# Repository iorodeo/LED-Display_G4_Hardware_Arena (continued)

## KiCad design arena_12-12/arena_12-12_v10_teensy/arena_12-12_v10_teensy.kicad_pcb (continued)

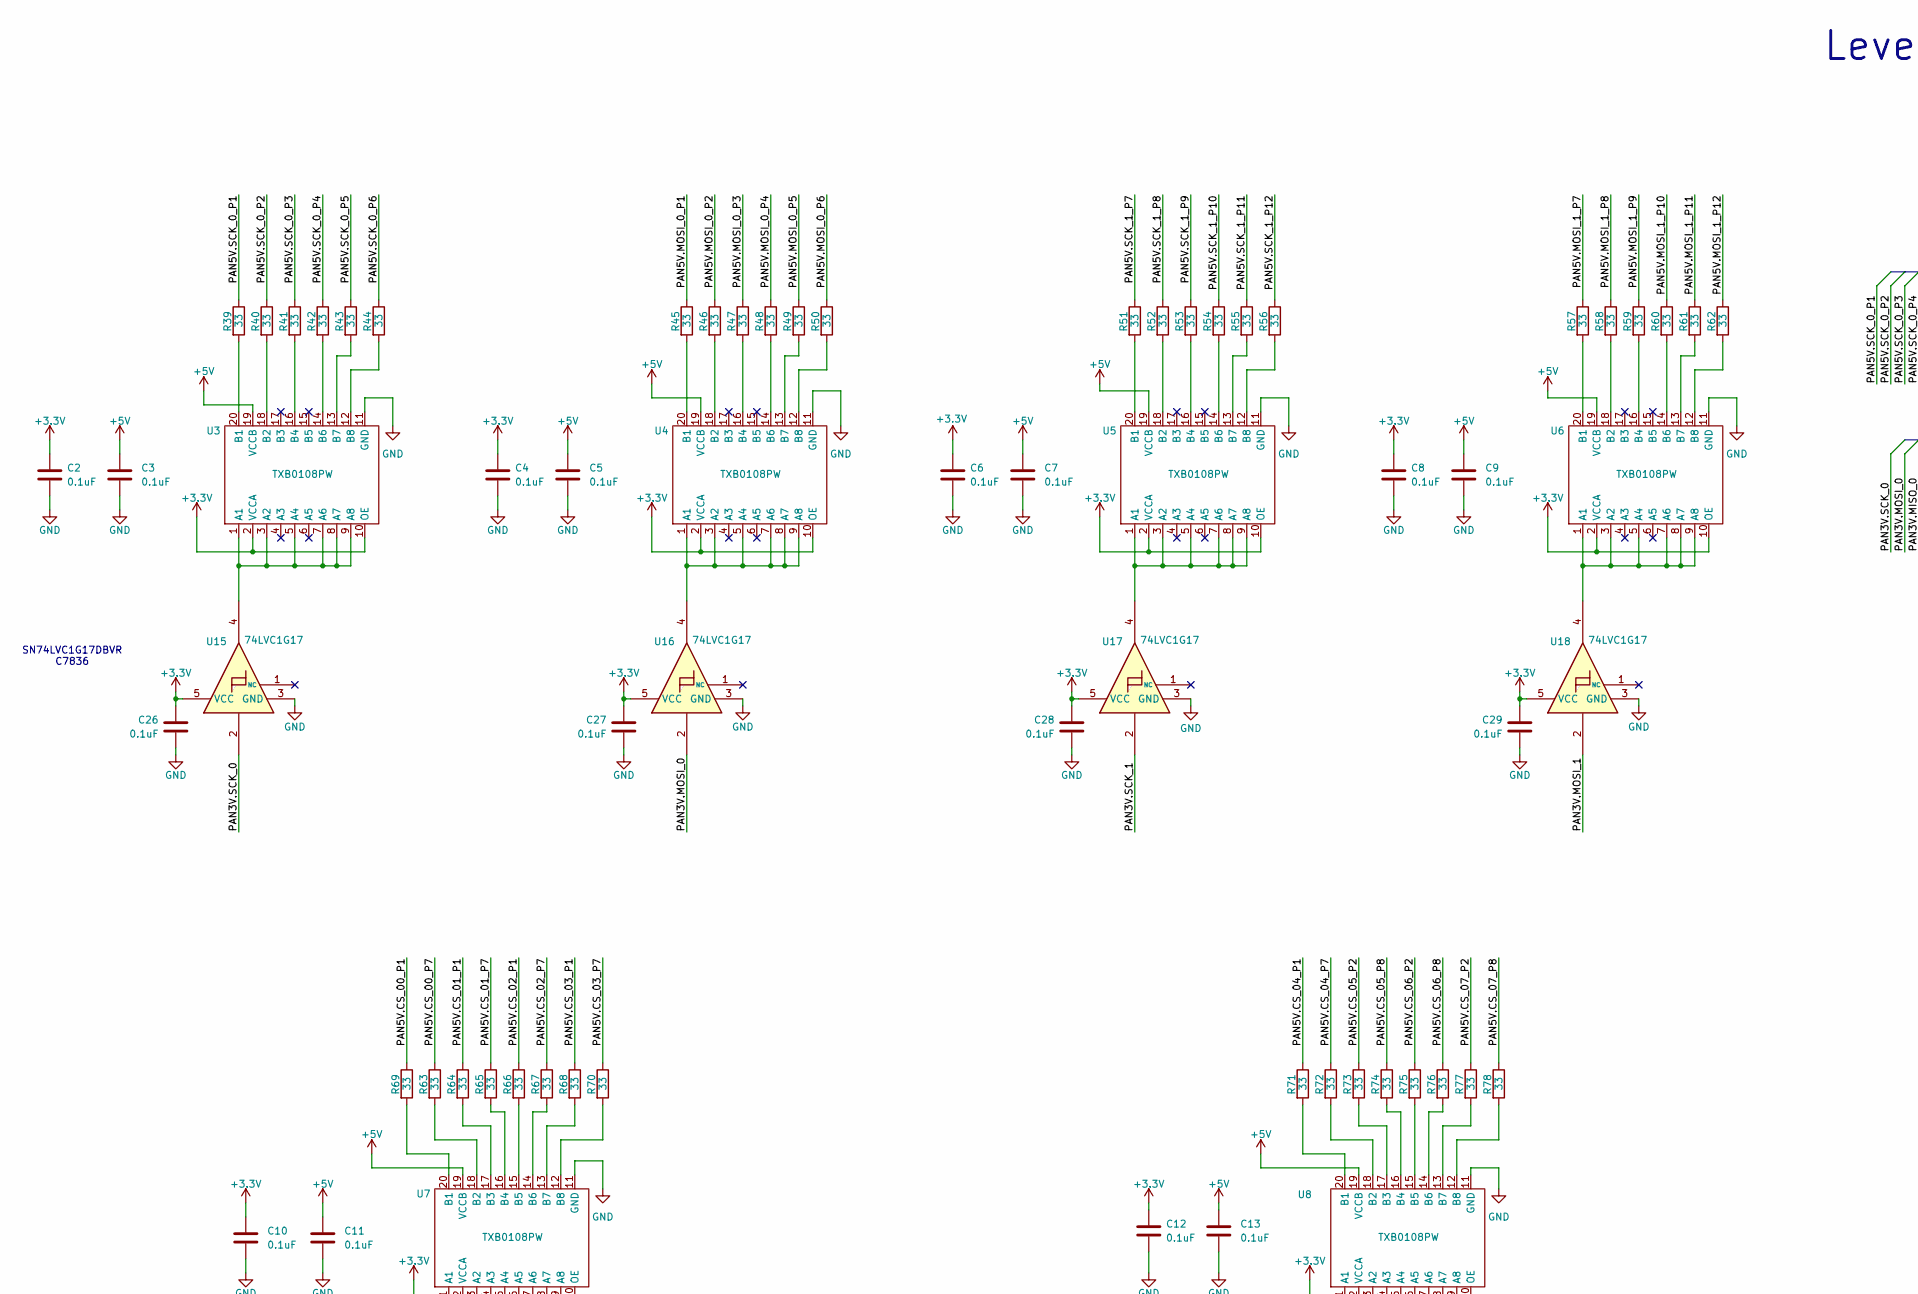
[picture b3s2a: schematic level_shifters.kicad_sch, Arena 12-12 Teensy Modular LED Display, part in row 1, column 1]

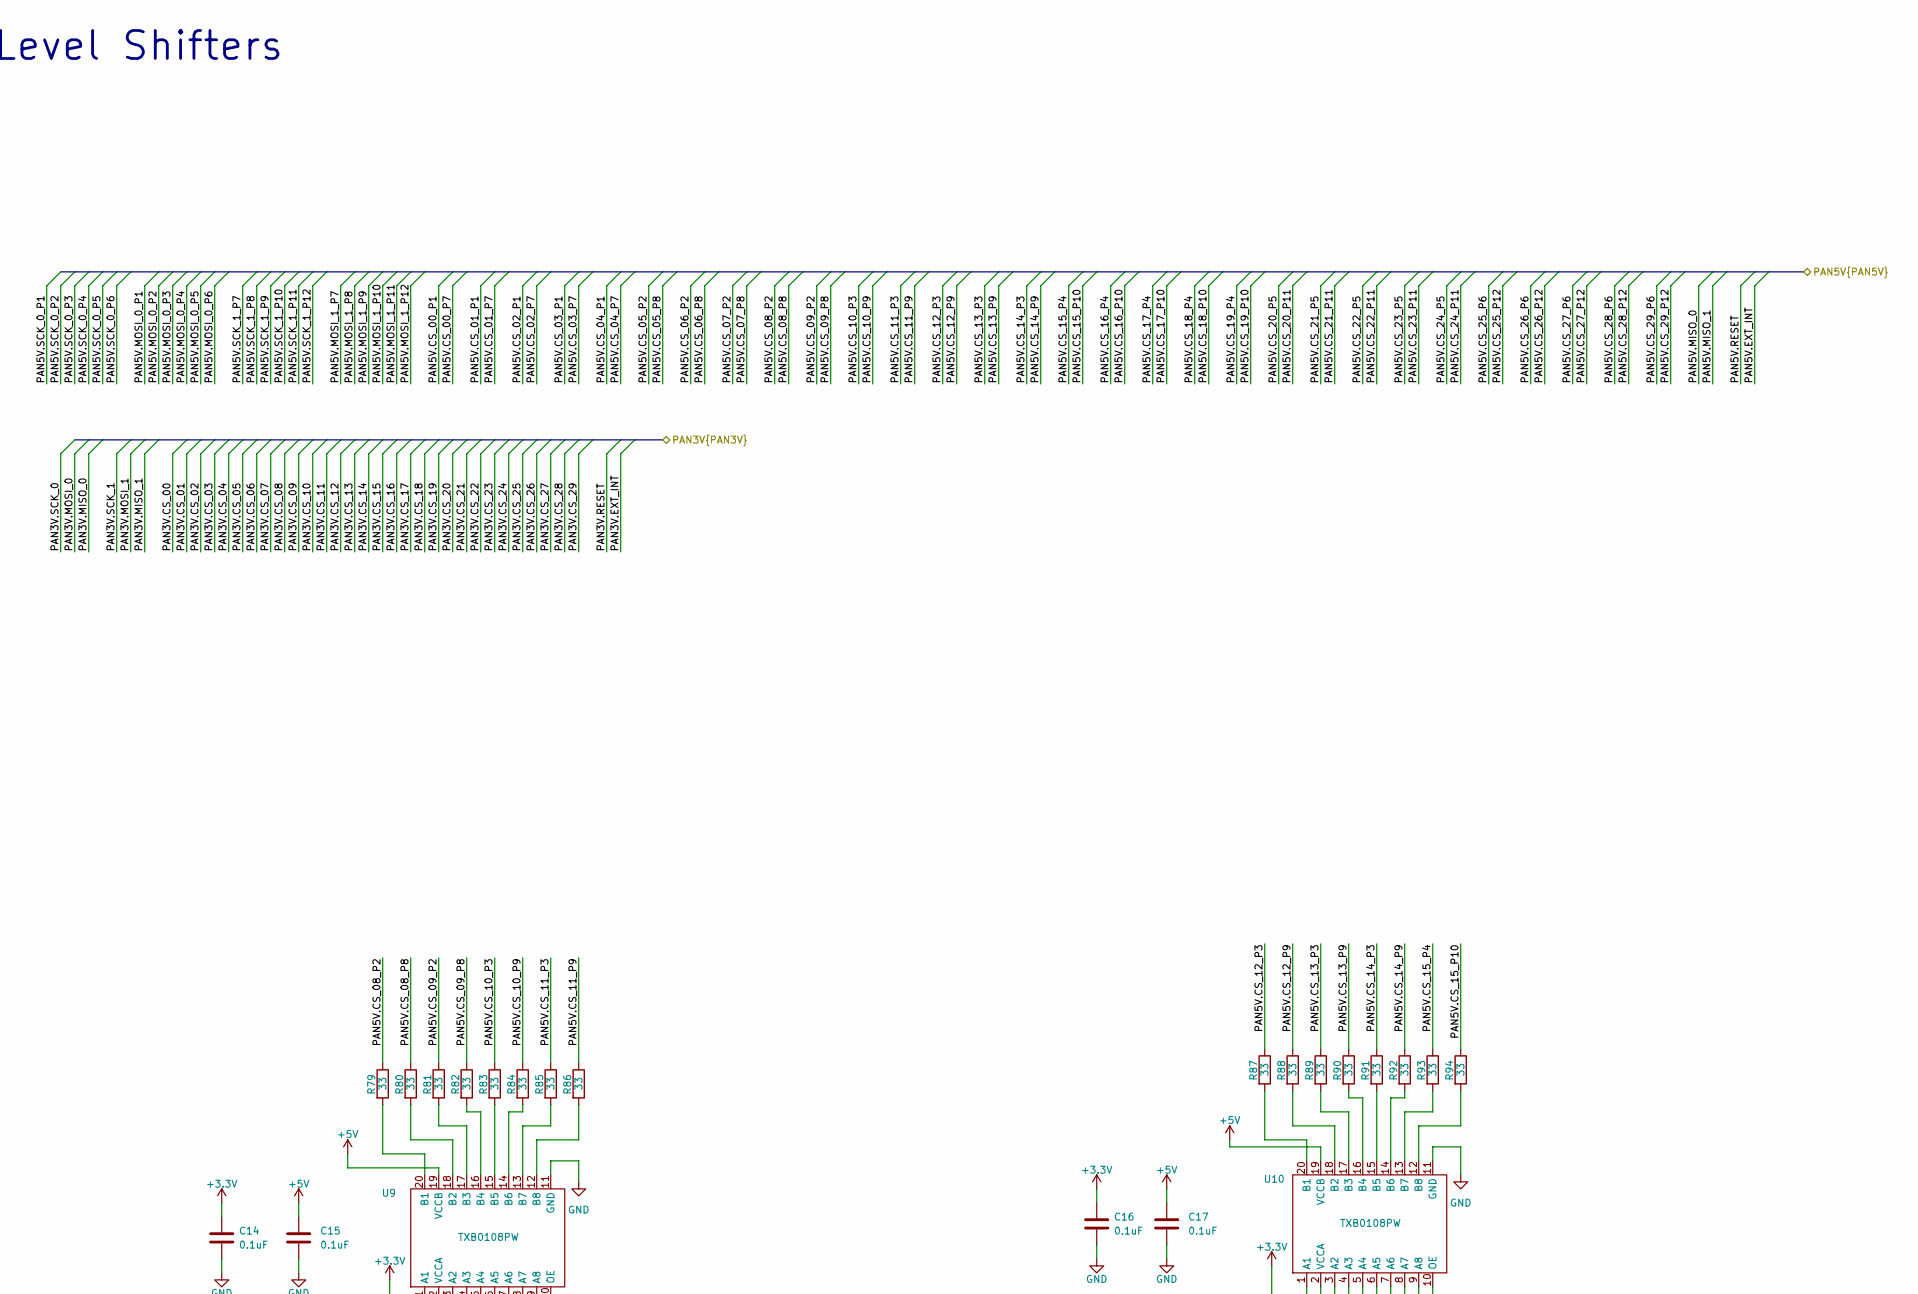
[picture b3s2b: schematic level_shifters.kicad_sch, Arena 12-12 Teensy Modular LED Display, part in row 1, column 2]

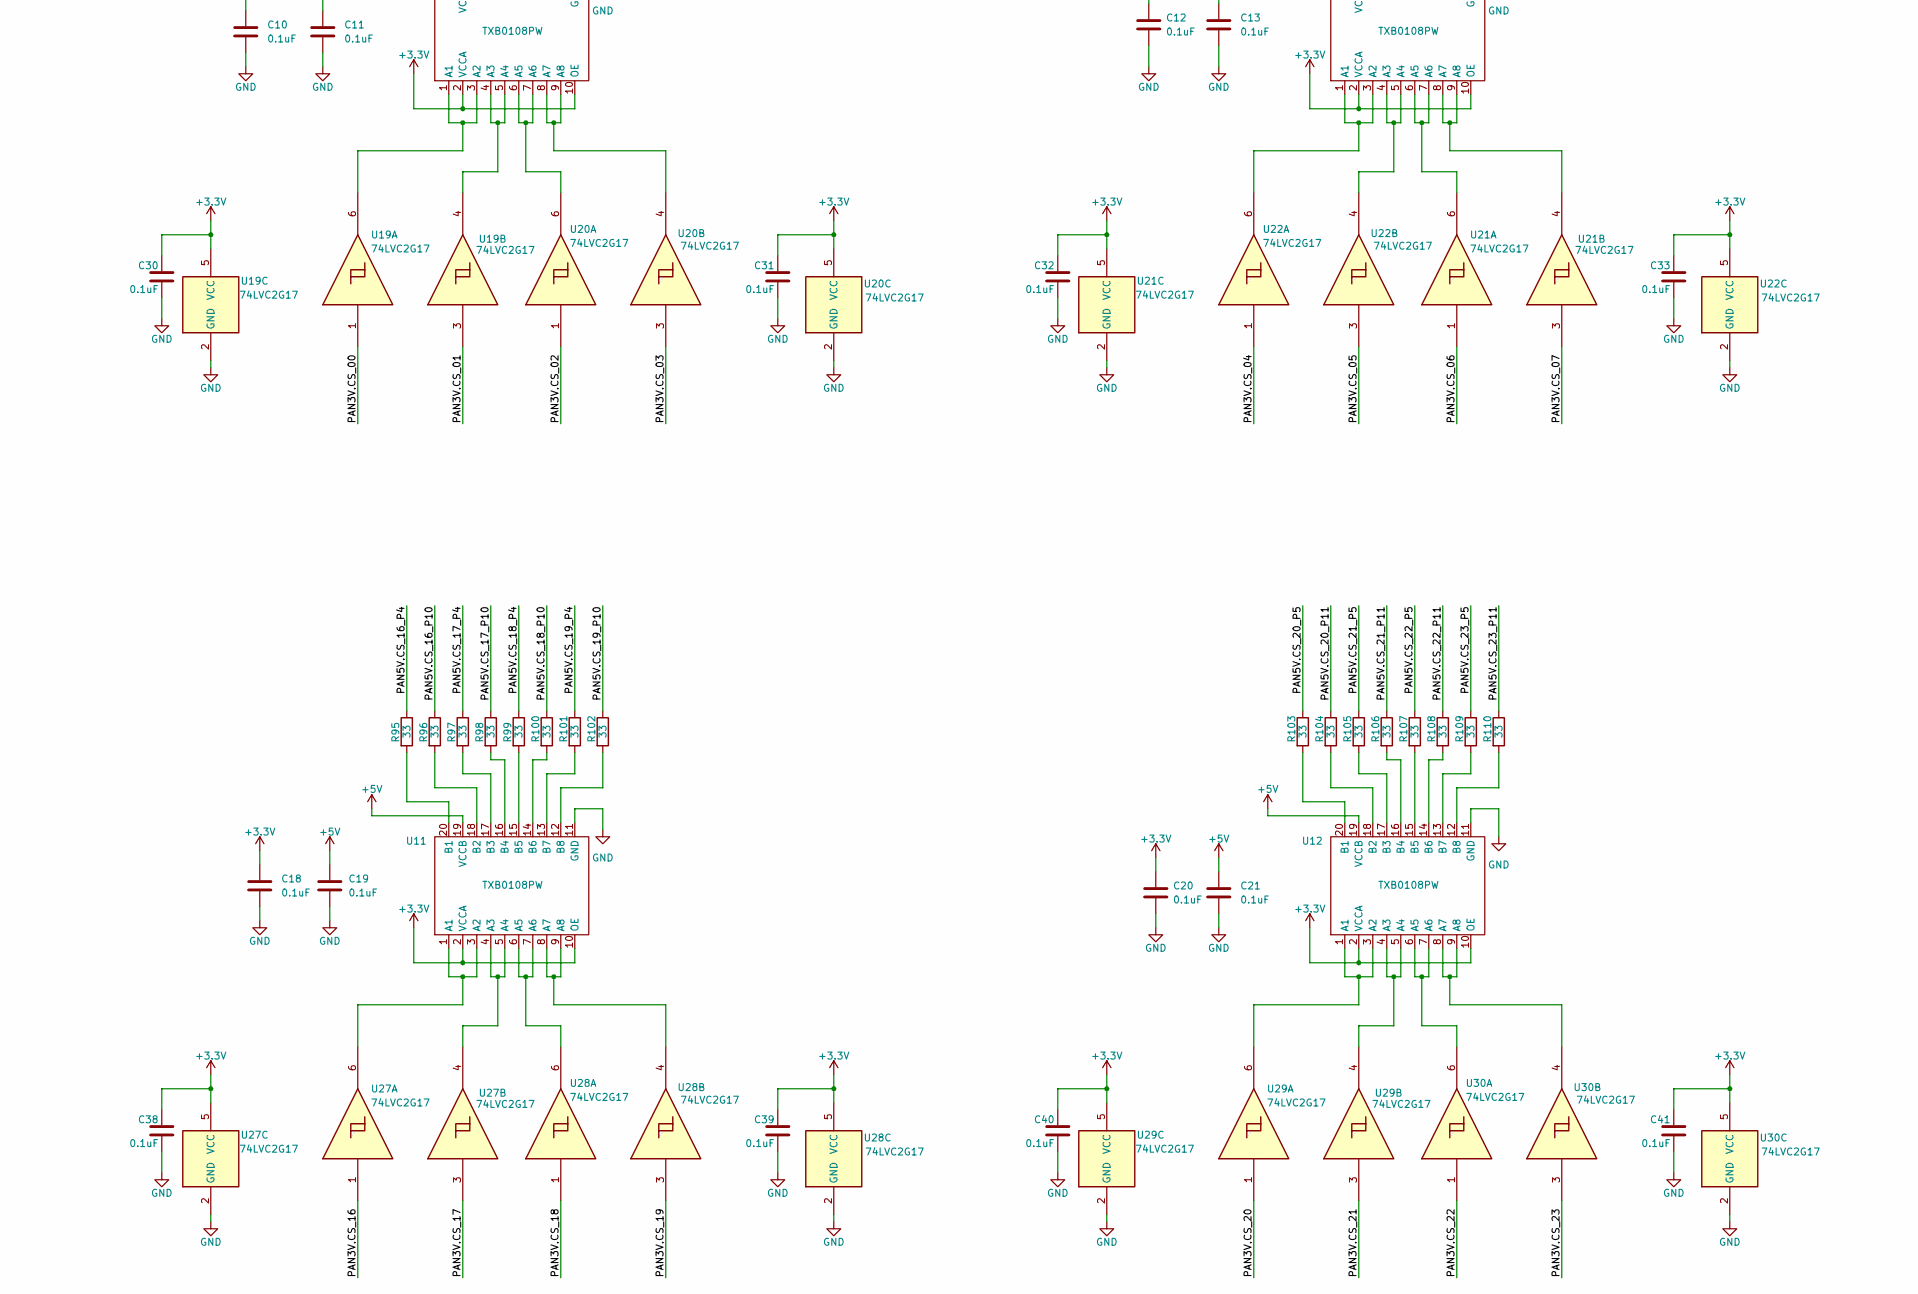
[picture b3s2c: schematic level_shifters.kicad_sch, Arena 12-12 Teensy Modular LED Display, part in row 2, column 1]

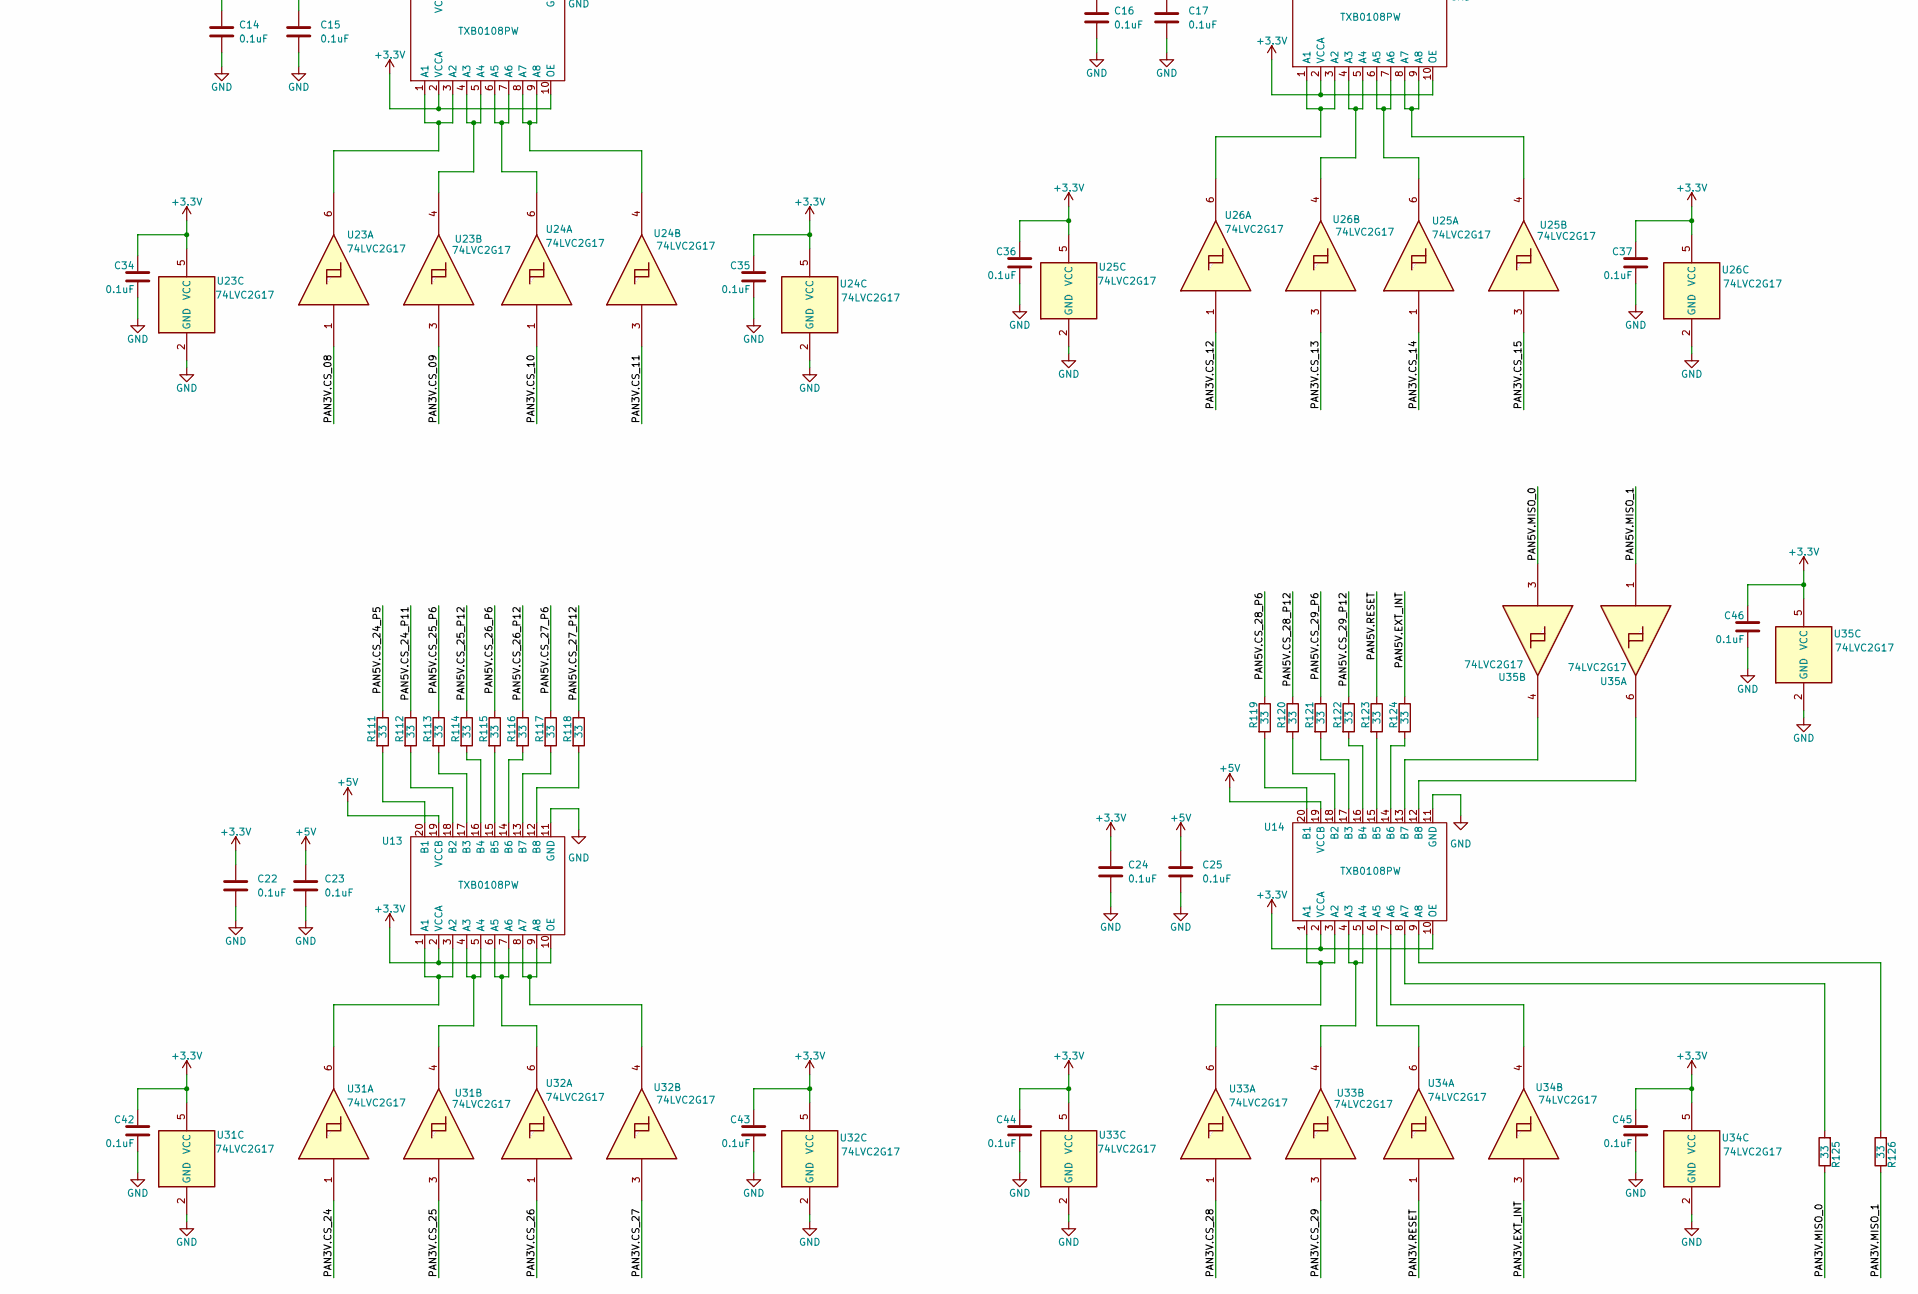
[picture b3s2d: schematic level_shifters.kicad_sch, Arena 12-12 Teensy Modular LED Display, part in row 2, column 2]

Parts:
C2, C3, C4, C5, C6, C7, C8, C9, C10, C11, C12, C13, C14, C15, C16, C17, C18, C19, C20, C21, C22, C23, C24, C25, C26, C27, C28, C29, C30, C31, C32, C33, C34, C35, C36, C37, C38, C39, C40, C41, C42, C43, C44, C45, C46: 0.1uF; C_0402_1005Metric; MPN CL05B104KO5NNNC; DigiKey PN 1276-1001-2-ND
R39, R40, R41, R42, R43, R44, R45, R46, R47, R48, R49, R50, R51, R52, R53, R54, R55, R56, R57, R58, R59, R60, R61, R62, R63, R64, R65, R66, R67, R68, R69, R70, R71, R72, R73, R74, R75, R76, R77, R78, R79, R80, R81, R82, R83, R84, R85, R86, R87, R88, R89, R90, R91, R92, R93, R94, R95, R96, R97, R98, R99, R100, R101, R102, R103, R104, R105, R106, R107, R108, R109, R110, R111, R112, R113, R114, R115, R116, R117, R118, R119, R120, R121, R122, R123, R124, R125, R126: 33; R_0402_1005Metric; MPN 0402WGF330JTCE; LCSC Part # C25105
U3, U4, U5, U6, U7, U8, U9, U10, U11, U12, U13, U14: TXB0108PW; TSSOP-20_4.4x6.5mm_P0.65mm; MPN TXB0108PWR; DigiKey PN 296-21527-2-ND
U15, U16, U17, U18: 74LVC1G17; SOT-23-5; MPN SN74LVC1G17DBVR; DigiKey PN 296-11933-2-ND
U19, U20, U21, U22, U23, U24, U25, U26, U27, U28, U29, U30, U31, U32, U33, U34, U35: 74LVC2G17; SOT-23-6; MPN SN74LVC2G17DBVR; DigiKey PN 296-SN74LVC2G17DBVRTR-ND

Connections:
+3.3V: C2.1, C4.1, C6.1, C8.1, C10.1, C12.1, C14.1, C16.1, C18.1, C20.1, C22.1, C24.1, C26.1, C27.1, C28.1, C29.1, C30.1, C31.1, C32.1, C33.1, C34.1, C35.1, C36.1, C37.1, C38.1, C39.1, C40.1, C41.1, C42.1, C43.1, C44.1, C45.1, C46.1, U3.2 (VCCA), U3.10 (OE), U4.2 (VCCA), U4.10 (OE), U5.2 (VCCA), U5.10 (OE), U6.2 (VCCA), U6.10 (OE), U7.2 (VCCA), U7.10 (OE), U8.2 (VCCA), U8.10 (OE), U9.2 (VCCA), U9.10 (OE), U10.2 (VCCA), U10.10 (OE), U11.2 (VCCA), U11.10 (OE), U12.2 (VCCA), U12.10 (OE), U13.2 (VCCA), U13.10 (OE), U14.2 (VCCA), U14.10 (OE), U15.5 (VCC), U16.5 (VCC), U17.5 (VCC), U18.5 (VCC), U19.5 (VCC), U20.5 (VCC), U21.5 (VCC), U22.5 (VCC), U23.5 (VCC), U24.5 (VCC), U25.5 (VCC), U26.5 (VCC), U27.5 (VCC), U28.5 (VCC), U29.5 (VCC), U30.5 (VCC), U31.5 (VCC), U32.5 (VCC), U33.5 (VCC), U34.5 (VCC), U35.5 (VCC); also elsewhere on the board
+5V: C3.1, C5.1, C7.1, C9.1, C11.1, C13.1, C15.1, C17.1, C19.1, C21.1, C23.1, C25.1, U3.19 (VCCB), U4.19 (VCCB), U5.19 (VCCB), U6.19 (VCCB), U7.19 (VCCB), U8.19 (VCCB), U9.19 (VCCB), U10.19 (VCCB), U11.19 (VCCB), U12.19 (VCCB), U13.19 (VCCB), U14.19 (VCCB); also elsewhere on the board
/Level Shifters/PAN3V.CS_00: U19.1; also elsewhere on the board
/Level Shifters/PAN3V.CS_01: U19.3; also elsewhere on the board
/Level Shifters/PAN3V.CS_02: U20.1; also elsewhere on the board
/Level Shifters/PAN3V.CS_03: U20.3; also elsewhere on the board
/Level Shifters/PAN3V.CS_04: U22.1; also elsewhere on the board
/Level Shifters/PAN3V.CS_05: U22.3; also elsewhere on the board
/Level Shifters/PAN3V.CS_06: U21.1; also elsewhere on the board
/Level Shifters/PAN3V.CS_07: U21.3; also elsewhere on the board
/Level Shifters/PAN3V.CS_08: U23.1; also elsewhere on the board
/Level Shifters/PAN3V.CS_09: U23.3; also elsewhere on the board
/Level Shifters/PAN3V.CS_10: U24.1; also elsewhere on the board
/Level Shifters/PAN3V.CS_11: U24.3; also elsewhere on the board
/Level Shifters/PAN3V.CS_12: U26.1; also elsewhere on the board
/Level Shifters/PAN3V.CS_13: U26.3; also elsewhere on the board
/Level Shifters/PAN3V.CS_14: U25.1; also elsewhere on the board
/Level Shifters/PAN3V.CS_15: U25.3; also elsewhere on the board
/Level Shifters/PAN3V.CS_16: U27.1; also elsewhere on the board
/Level Shifters/PAN3V.CS_17: U27.3; also elsewhere on the board
/Level Shifters/PAN3V.CS_18: U28.1; also elsewhere on the board
/Level Shifters/PAN3V.CS_19: U28.3; also elsewhere on the board
/Level Shifters/PAN3V.CS_20: U29.1; also elsewhere on the board
/Level Shifters/PAN3V.CS_21: U29.3; also elsewhere on the board
/Level Shifters/PAN3V.CS_22: U30.1; also elsewhere on the board
/Level Shifters/PAN3V.CS_23: U30.3; also elsewhere on the board
/Level Shifters/PAN3V.CS_24: U31.1; also elsewhere on the board
/Level Shifters/PAN3V.CS_25: U31.3; also elsewhere on the board
/Level Shifters/PAN3V.CS_26: U32.1; also elsewhere on the board
/Level Shifters/PAN3V.CS_27: U32.3; also elsewhere on the board
/Level Shifters/PAN3V.CS_28: U33.1; also elsewhere on the board
/Level Shifters/PAN3V.CS_29: U33.3; also elsewhere on the board
/Level Shifters/PAN3V.EXT_INT: U34.3; also elsewhere on the board
/Level Shifters/PAN3V.MISO_0: R125.1; also elsewhere on the board
/Level Shifters/PAN3V.MISO_1: R126.1; also elsewhere on the board
/Level Shifters/PAN3V.MOSI_0: U16.2; also elsewhere on the board
/Level Shifters/PAN3V.MOSI_1: U18.2; also elsewhere on the board
/Level Shifters/PAN3V.RESET: U34.1; also elsewhere on the board
/Level Shifters/PAN3V.SCK_0: U15.2; also elsewhere on the board
/Level Shifters/PAN3V.SCK_1: U17.2; also elsewhere on the board
/Level Shifters/PAN5V.CS_00_P1: R69.1; also elsewhere on the board
/Level Shifters/PAN5V.CS_00_P7: R63.1; also elsewhere on the board
/Level Shifters/PAN5V.CS_01_P1: R64.1; also elsewhere on the board
/Level Shifters/PAN5V.CS_01_P7: R65.1; also elsewhere on the board
/Level Shifters/PAN5V.CS_02_P1: R66.1; also elsewhere on the board
/Level Shifters/PAN5V.CS_02_P7: R67.1; also elsewhere on the board
/Level Shifters/PAN5V.CS_03_P1: R68.1; also elsewhere on the board
/Level Shifters/PAN5V.CS_03_P7: R70.1; also elsewhere on the board
/Level Shifters/PAN5V.CS_04_P1: R71.1; also elsewhere on the board
/Level Shifters/PAN5V.CS_04_P7: R72.1; also elsewhere on the board
/Level Shifters/PAN5V.CS_05_P2: R73.1; also elsewhere on the board
/Level Shifters/PAN5V.CS_05_P8: R74.1; also elsewhere on the board
/Level Shifters/PAN5V.CS_06_P2: R75.1; also elsewhere on the board
/Level Shifters/PAN5V.CS_06_P8: R76.1; also elsewhere on the board
/Level Shifters/PAN5V.CS_07_P2: R77.1; also elsewhere on the board
/Level Shifters/PAN5V.CS_07_P8: R78.1; also elsewhere on the board
/Level Shifters/PAN5V.CS_08_P2: R79.1; also elsewhere on the board
/Level Shifters/PAN5V.CS_08_P8: R80.1; also elsewhere on the board
/Level Shifters/PAN5V.CS_09_P2: R81.1; also elsewhere on the board
/Level Shifters/PAN5V.CS_09_P8: R82.1; also elsewhere on the board
/Level Shifters/PAN5V.CS_10_P3: R83.1; also elsewhere on the board
/Level Shifters/PAN5V.CS_10_P9: R84.1; also elsewhere on the board
/Level Shifters/PAN5V.CS_11_P3: R85.1; also elsewhere on the board
/Level Shifters/PAN5V.CS_11_P9: R86.1; also elsewhere on the board
/Level Shifters/PAN5V.CS_12_P3: R87.1; also elsewhere on the board
/Level Shifters/PAN5V.CS_12_P9: R88.1; also elsewhere on the board
/Level Shifters/PAN5V.CS_13_P3: R89.1; also elsewhere on the board
/Level Shifters/PAN5V.CS_13_P9: R90.1; also elsewhere on the board
/Level Shifters/PAN5V.CS_14_P3: R91.1; also elsewhere on the board
/Level Shifters/PAN5V.CS_14_P9: R92.1; also elsewhere on the board
/Level Shifters/PAN5V.CS_15_P4: R93.1; also elsewhere on the board
/Level Shifters/PAN5V.CS_15_P10: R94.1; also elsewhere on the board
/Level Shifters/PAN5V.CS_16_P4: R95.1; also elsewhere on the board
/Level Shifters/PAN5V.CS_16_P10: R96.1; also elsewhere on the board
/Level Shifters/PAN5V.CS_17_P4: R97.1; also elsewhere on the board
/Level Shifters/PAN5V.CS_17_P10: R98.1; also elsewhere on the board
/Level Shifters/PAN5V.CS_18_P4: R99.1; also elsewhere on the board
/Level Shifters/PAN5V.CS_18_P10: R100.1; also elsewhere on the board
/Level Shifters/PAN5V.CS_19_P4: R101.1; also elsewhere on the board
/Level Shifters/PAN5V.CS_19_P10: R102.1; also elsewhere on the board
/Level Shifters/PAN5V.CS_20_P5: R103.1; also elsewhere on the board
/Level Shifters/PAN5V.CS_20_P11: R104.1; also elsewhere on the board
/Level Shifters/PAN5V.CS_21_P5: R105.1; also elsewhere on the board
/Level Shifters/PAN5V.CS_21_P11: R106.1; also elsewhere on the board
/Level Shifters/PAN5V.CS_22_P5: R107.1; also elsewhere on the board
/Level Shifters/PAN5V.CS_22_P11: R108.1; also elsewhere on the board
/Level Shifters/PAN5V.CS_23_P5: R109.1; also elsewhere on the board
/Level Shifters/PAN5V.CS_23_P11: R110.1; also elsewhere on the board
/Level Shifters/PAN5V.CS_24_P5: R111.1; also elsewhere on the board
/Level Shifters/PAN5V.CS_24_P11: R112.1; also elsewhere on the board
/Level Shifters/PAN5V.CS_25_P6: R113.1; also elsewhere on the board
/Level Shifters/PAN5V.CS_25_P12: R114.1; also elsewhere on the board
/Level Shifters/PAN5V.CS_26_P6: R115.1; also elsewhere on the board
/Level Shifters/PAN5V.CS_26_P12: R116.1; also elsewhere on the board
/Level Shifters/PAN5V.CS_27_P6: R117.1; also elsewhere on the board
/Level Shifters/PAN5V.CS_27_P12: R118.1; also elsewhere on the board
/Level Shifters/PAN5V.CS_28_P6: R119.1; also elsewhere on the board
/Level Shifters/PAN5V.CS_28_P12: R120.1; also elsewhere on the board
/Level Shifters/PAN5V.CS_29_P6: R121.1; also elsewhere on the board
/Level Shifters/PAN5V.CS_29_P12: R122.1; also elsewhere on the board
/Level Shifters/PAN5V.EXT_INT: R124.1; also elsewhere on the board
/Level Shifters/PAN5V.MISO_0: U35.3; also elsewhere on the board
/Level Shifters/PAN5V.MISO_1: U35.1; also elsewhere on the board
/Level Shifters/PAN5V.MOSI_0_P1: R45.1; also elsewhere on the board
/Level Shifters/PAN5V.MOSI_0_P2: R46.1; also elsewhere on the board
/Level Shifters/PAN5V.MOSI_0_P3: R47.1; also elsewhere on the board
/Level Shifters/PAN5V.MOSI_0_P4: R48.1; also elsewhere on the board
/Level Shifters/PAN5V.MOSI_0_P5: R49.1; also elsewhere on the board
/Level Shifters/PAN5V.MOSI_0_P6: R50.1; also elsewhere on the board
/Level Shifters/PAN5V.MOSI_1_P7: R57.1; also elsewhere on the board
/Level Shifters/PAN5V.MOSI_1_P8: R58.1; also elsewhere on the board
/Level Shifters/PAN5V.MOSI_1_P9: R59.1; also elsewhere on the board
/Level Shifters/PAN5V.MOSI_1_P10: R60.1; also elsewhere on the board
/Level Shifters/PAN5V.MOSI_1_P11: R61.1; also elsewhere on the board
/Level Shifters/PAN5V.MOSI_1_P12: R62.1; also elsewhere on the board
/Level Shifters/PAN5V.RESET: R123.1; also elsewhere on the board
/Level Shifters/PAN5V.SCK_0_P1: R39.1; also elsewhere on the board
/Level Shifters/PAN5V.SCK_0_P2: R40.1; also elsewhere on the board
/Level Shifters/PAN5V.SCK_0_P3: R41.1; also elsewhere on the board
/Level Shifters/PAN5V.SCK_0_P4: R42.1; also elsewhere on the board
/Level Shifters/PAN5V.SCK_0_P5: R43.1; also elsewhere on the board
/Level Shifters/PAN5V.SCK_0_P6: R44.1; also elsewhere on the board
/Level Shifters/PAN5V.SCK_1_P7: R51.1; also elsewhere on the board
/Level Shifters/PAN5V.SCK_1_P8: R52.1; also elsewhere on the board
/Level Shifters/PAN5V.SCK_1_P9: R53.1; also elsewhere on the board
/Level Shifters/PAN5V.SCK_1_P10: R54.1; also elsewhere on the board
/Level Shifters/PAN5V.SCK_1_P11: R55.1; also elsewhere on the board
/Level Shifters/PAN5V.SCK_1_P12: R56.1; also elsewhere on the board
GND: C2.2, C3.2, C4.2, C5.2, C6.2, C7.2, C8.2, C9.2, C10.2, C11.2, C12.2, C13.2, C14.2, C15.2, C16.2, C17.2, C18.2, C19.2, C20.2, C21.2, C22.2, C23.2, C24.2, C25.2, C26.2, C27.2, C28.2, C29.2, C30.2, C31.2, C32.2, C33.2, C34.2, C35.2, C36.2, C37.2, C38.2, C39.2, C40.2, C41.2, C42.2, C43.2, C44.2, C45.2, C46.2, U3.11 (GND), U4.11 (GND), U5.11 (GND), U6.11 (GND), U7.11 (GND), U8.11 (GND), U9.11 (GND), U10.11 (GND), U11.11 (GND), U12.11 (GND), U13.11 (GND), U14.11 (GND), U15.3 (GND), U16.3 (GND), U17.3 (GND), U18.3 (GND), U19.2 (GND), U20.2 (GND), U21.2 (GND), U22.2 (GND), U23.2 (GND), U24.2 (GND), U25.2 (GND), U26.2 (GND), U27.2 (GND), U28.2 (GND), U29.2 (GND), U30.2 (GND), U31.2 (GND), U32.2 (GND), U33.2 (GND), U34.2 (GND), U35.2 (GND); also elsewhere on the board
unnamed: U3.1 (A1), U3.3 (A2), U3.5 (A4), U3.7 (A6), U3.8 (A7), U3.9 (A8), U15.4
unnamed: R39.2, U3.20 (B1)
unnamed: R40.2, U3.18 (B2)
unnamed: R41.2, U3.16 (B4)
unnamed: R42.2, U3.14 (B6)
unnamed: R43.2, U3.13 (B7)
unnamed: R44.2, U3.12 (B8)
unnamed: U4.1 (A1), U4.3 (A2), U4.5 (A4), U4.7 (A6), U4.8 (A7), U4.9 (A8), U16.4
unnamed: R45.2, U4.20 (B1)
unnamed: R46.2, U4.18 (B2)
unnamed: R47.2, U4.16 (B4)
unnamed: R48.2, U4.14 (B6)
unnamed: R49.2, U4.13 (B7)
unnamed: R50.2, U4.12 (B8)
unnamed: U5.1 (A1), U5.3 (A2), U5.5 (A4), U5.7 (A6), U5.8 (A7), U5.9 (A8), U17.4
unnamed: R51.2, U5.20 (B1)
unnamed: R52.2, U5.18 (B2)
unnamed: R53.2, U5.16 (B4)
unnamed: R54.2, U5.14 (B6)
unnamed: R55.2, U5.13 (B7)
unnamed: R56.2, U5.12 (B8)
unnamed: U6.1 (A1), U6.3 (A2), U6.5 (A4), U6.7 (A6), U6.8 (A7), U6.9 (A8), U18.4
unnamed: R57.2, U6.20 (B1)
unnamed: R58.2, U6.18 (B2)
unnamed: R59.2, U6.16 (B4)
unnamed: R60.2, U6.14 (B6)
unnamed: R61.2, U6.13 (B7)
unnamed: R62.2, U6.12 (B8)
unnamed: U7.1 (A1), U7.3 (A2), U19.6
unnamed: U7.4 (A3), U7.5 (A4), U19.4
unnamed: U7.6 (A5), U7.7 (A6), U20.6
unnamed: U7.8 (A7), U7.9 (A8), U20.4
unnamed: R69.2, U7.20 (B1)
unnamed: R63.2, U7.18 (B2)
unnamed: R64.2, U7.17 (B3)
unnamed: R65.2, U7.16 (B4)
unnamed: R66.2, U7.15 (B5)
unnamed: R67.2, U7.14 (B6)
unnamed: R68.2, U7.13 (B7)
unnamed: R70.2, U7.12 (B8)
unnamed: U8.1 (A1), U8.3 (A2), U22.6
unnamed: U8.4 (A3), U8.5 (A4), U22.4
unnamed: U8.6 (A5), U8.7 (A6), U21.6
unnamed: U8.8 (A7), U8.9 (A8), U21.4
unnamed: R71.2, U8.20 (B1)
unnamed: R72.2, U8.18 (B2)
unnamed: R73.2, U8.17 (B3)
unnamed: R74.2, U8.16 (B4)
unnamed: R75.2, U8.15 (B5)
unnamed: R76.2, U8.14 (B6)
unnamed: R77.2, U8.13 (B7)
unnamed: R78.2, U8.12 (B8)
unnamed: U9.1 (A1), U9.3 (A2), U23.6
unnamed: U9.4 (A3), U9.5 (A4), U23.4
unnamed: U9.6 (A5), U9.7 (A6), U24.6
unnamed: U9.8 (A7), U9.9 (A8), U24.4
unnamed: R79.2, U9.20 (B1)
unnamed: R80.2, U9.18 (B2)
unnamed: R81.2, U9.17 (B3)
unnamed: R82.2, U9.16 (B4)
unnamed: R83.2, U9.15 (B5)
unnamed: R84.2, U9.14 (B6)
unnamed: R85.2, U9.13 (B7)
unnamed: R86.2, U9.12 (B8)
unnamed: U10.1 (A1), U10.3 (A2), U26.6
unnamed: U10.4 (A3), U10.5 (A4), U26.4
unnamed: U10.6 (A5), U10.7 (A6), U25.6
unnamed: U10.8 (A7), U10.9 (A8), U25.4
unnamed: R87.2, U10.20 (B1)
unnamed: R88.2, U10.18 (B2)
unnamed: R89.2, U10.17 (B3)
unnamed: R90.2, U10.16 (B4)
unnamed: R91.2, U10.15 (B5)
unnamed: R92.2, U10.14 (B6)
unnamed: R93.2, U10.13 (B7)
unnamed: R94.2, U10.12 (B8)
unnamed: U11.1 (A1), U11.3 (A2), U27.6
unnamed: U11.4 (A3), U11.5 (A4), U27.4
unnamed: U11.6 (A5), U11.7 (A6), U28.6
unnamed: U11.8 (A7), U11.9 (A8), U28.4
unnamed: R95.2, U11.20 (B1)
unnamed: R96.2, U11.18 (B2)
unnamed: R97.2, U11.17 (B3)
unnamed: R98.2, U11.16 (B4)
unnamed: R99.2, U11.15 (B5)
unnamed: R100.2, U11.14 (B6)
unnamed: R101.2, U11.13 (B7)
unnamed: R102.2, U11.12 (B8)
unnamed: U12.1 (A1), U12.3 (A2), U29.6
unnamed: U12.4 (A3), U12.5 (A4), U29.4
unnamed: U12.6 (A5), U12.7 (A6), U30.6
unnamed: U12.8 (A7), U12.9 (A8), U30.4
unnamed: R103.2, U12.20 (B1)
unnamed: R104.2, U12.18 (B2)
unnamed: R105.2, U12.17 (B3)
unnamed: R106.2, U12.16 (B4)
unnamed: R107.2, U12.15 (B5)
unnamed: R108.2, U12.14 (B6)
unnamed: R109.2, U12.13 (B7)
unnamed: R110.2, U12.12 (B8)
unnamed: U13.1 (A1), U13.3 (A2), U31.6
unnamed: U13.4 (A3), U13.5 (A4), U31.4
unnamed: U13.6 (A5), U13.7 (A6), U32.6
unnamed: U13.8 (A7), U13.9 (A8), U32.4
unnamed: R111.2, U13.20 (B1)
unnamed: R112.2, U13.18 (B2)
unnamed: R113.2, U13.17 (B3)
unnamed: R114.2, U13.16 (B4)
unnamed: R115.2, U13.15 (B5)
unnamed: R116.2, U13.14 (B6)
unnamed: R117.2, U13.13 (B7)
unnamed: R118.2, U13.12 (B8)
unnamed: U14.1 (A1), U14.3 (A2), U33.6
unnamed: U14.4 (A3), U14.5 (A4), U33.4
unnamed: U14.6 (A5), U34.6
unnamed: U14.7 (A6), U34.4
unnamed: R125.2, U14.8 (A7)
unnamed: R126.2, U14.9 (A8)
unnamed: R119.2, U14.20 (B1)
unnamed: R120.2, U14.18 (B2)
unnamed: R121.2, U14.17 (B3)
unnamed: R122.2, U14.16 (B4)
unnamed: R123.2, U14.15 (B5)
unnamed: R124.2, U14.14 (B6)
unnamed: U14.13 (B7), U35.4
unnamed: U14.12 (B8), U35.6

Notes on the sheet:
SN74LVC1G17DBVR C7836
Level Shifters

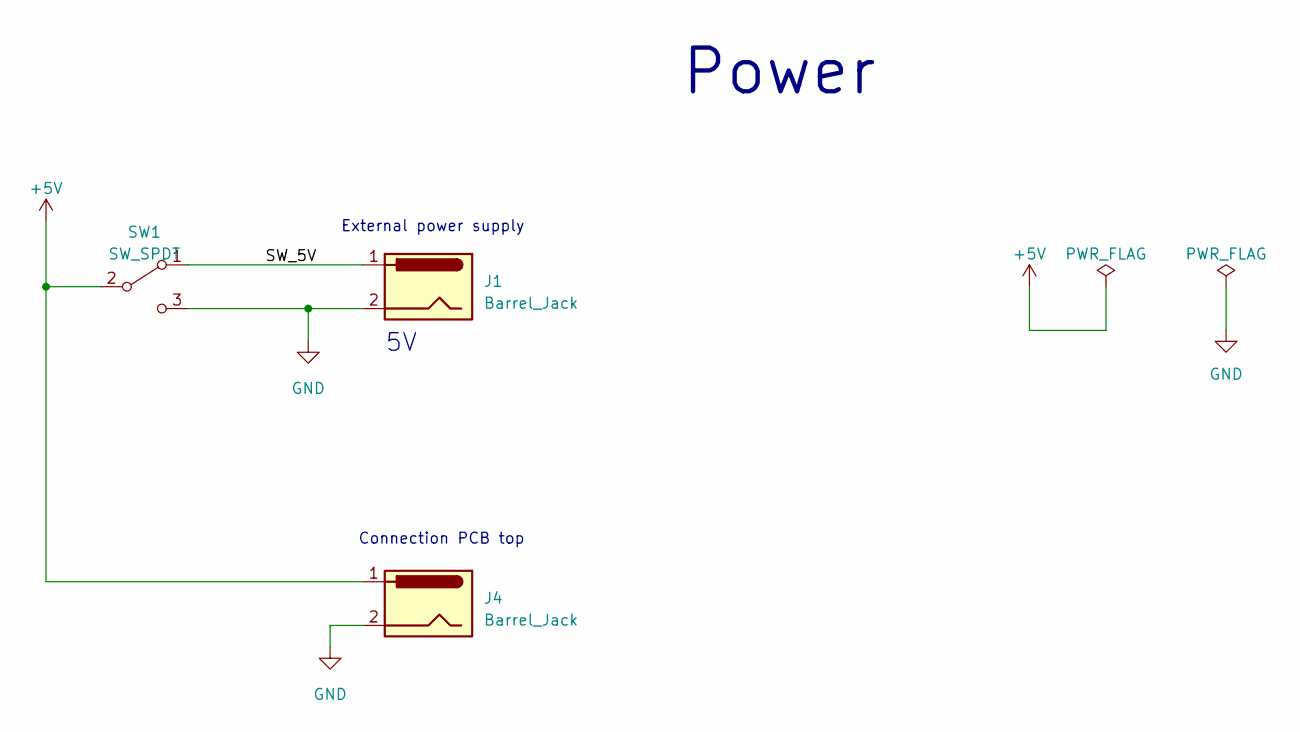
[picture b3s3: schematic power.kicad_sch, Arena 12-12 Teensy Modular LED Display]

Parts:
J1, J4: Barrel_Jack; DCJACK_2PIN_HIGHCURRENT; MPN PJ-063AH; DigiKey PN CP-063AH-ND
SW1: SW_SPDT; slide_switch; MPN L102021ML04Q; DigiKey PN CKC5102-ND

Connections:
+5V: J4.1, SW1.2 (B); also elsewhere on the board
/Power/SW_5V: J1.1, SW1.1 (A)
GND: J1.2, J4.2, SW1.3 (C); also elsewhere on the board

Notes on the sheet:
Connection PCB top
External power supply
Power

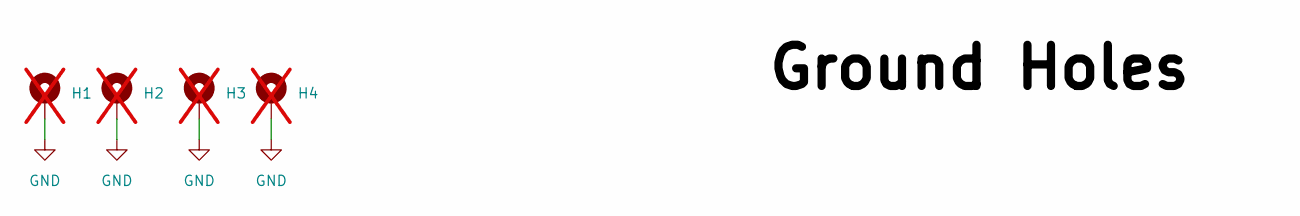
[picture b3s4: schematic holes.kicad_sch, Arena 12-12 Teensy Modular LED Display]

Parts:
H1, H2, H3, H4: MountingHole_Pad; MountingHole_4.5mm_Pad; not fitted

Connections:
GND: H1.1, H2.1, H3.1, H4.1; also elsewhere on the board
